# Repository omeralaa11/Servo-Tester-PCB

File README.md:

# Servo Tester PCB

A simple and compact servo tester based on the NE556 timer IC. This project includes a custom-designed PCB layout suitable for testing standard hobby servos.

## 🧰 Features

- Manual PWM signal generation using NE556 timer
- Adjustable pulse width via potentiometer
- Compatible with most RC servos
- Compact and easy-to-fabricate PCB design
- Powered via standard 5V input

## 📝 Project Files

This repository contains:

- `Servo_Tester.kicad_pcb` – PCB layout file (KiCad)
- `Servo_Tester.sch` – Schematic file (KiCad)
- `images/` – Rendered images of the PCB and schematic

## ⚙️ How It Works

The NE556 timer is configured in astable mode to generate a PWM signal. By adjusting the potentiometer, the pulse width of the PWM signal changes, thereby controlling the servo angle.

Typical PWM specs:
- Frequency: ~2.5KHz or 25KHz

## 🔧 Hardware Requirements

- NE556 timer IC
- 2*50k potentiometer
- Resistors and capacitors (see schematic)
- Standard 3-pin servo header
- 5V to 15V power source

## 📸 Gallery

## 🛠️ Usage

1. Connect a 5V power source to the input.
2. Plug in your servo to the output header (GND, VCC, Signal).
3. Rotate the potentiometer to test the servo movement.

## 🧑‍💻 Author

**Omer Alaa**  
🔗 [@omeralaa11](https://github.com/omeralaa11)

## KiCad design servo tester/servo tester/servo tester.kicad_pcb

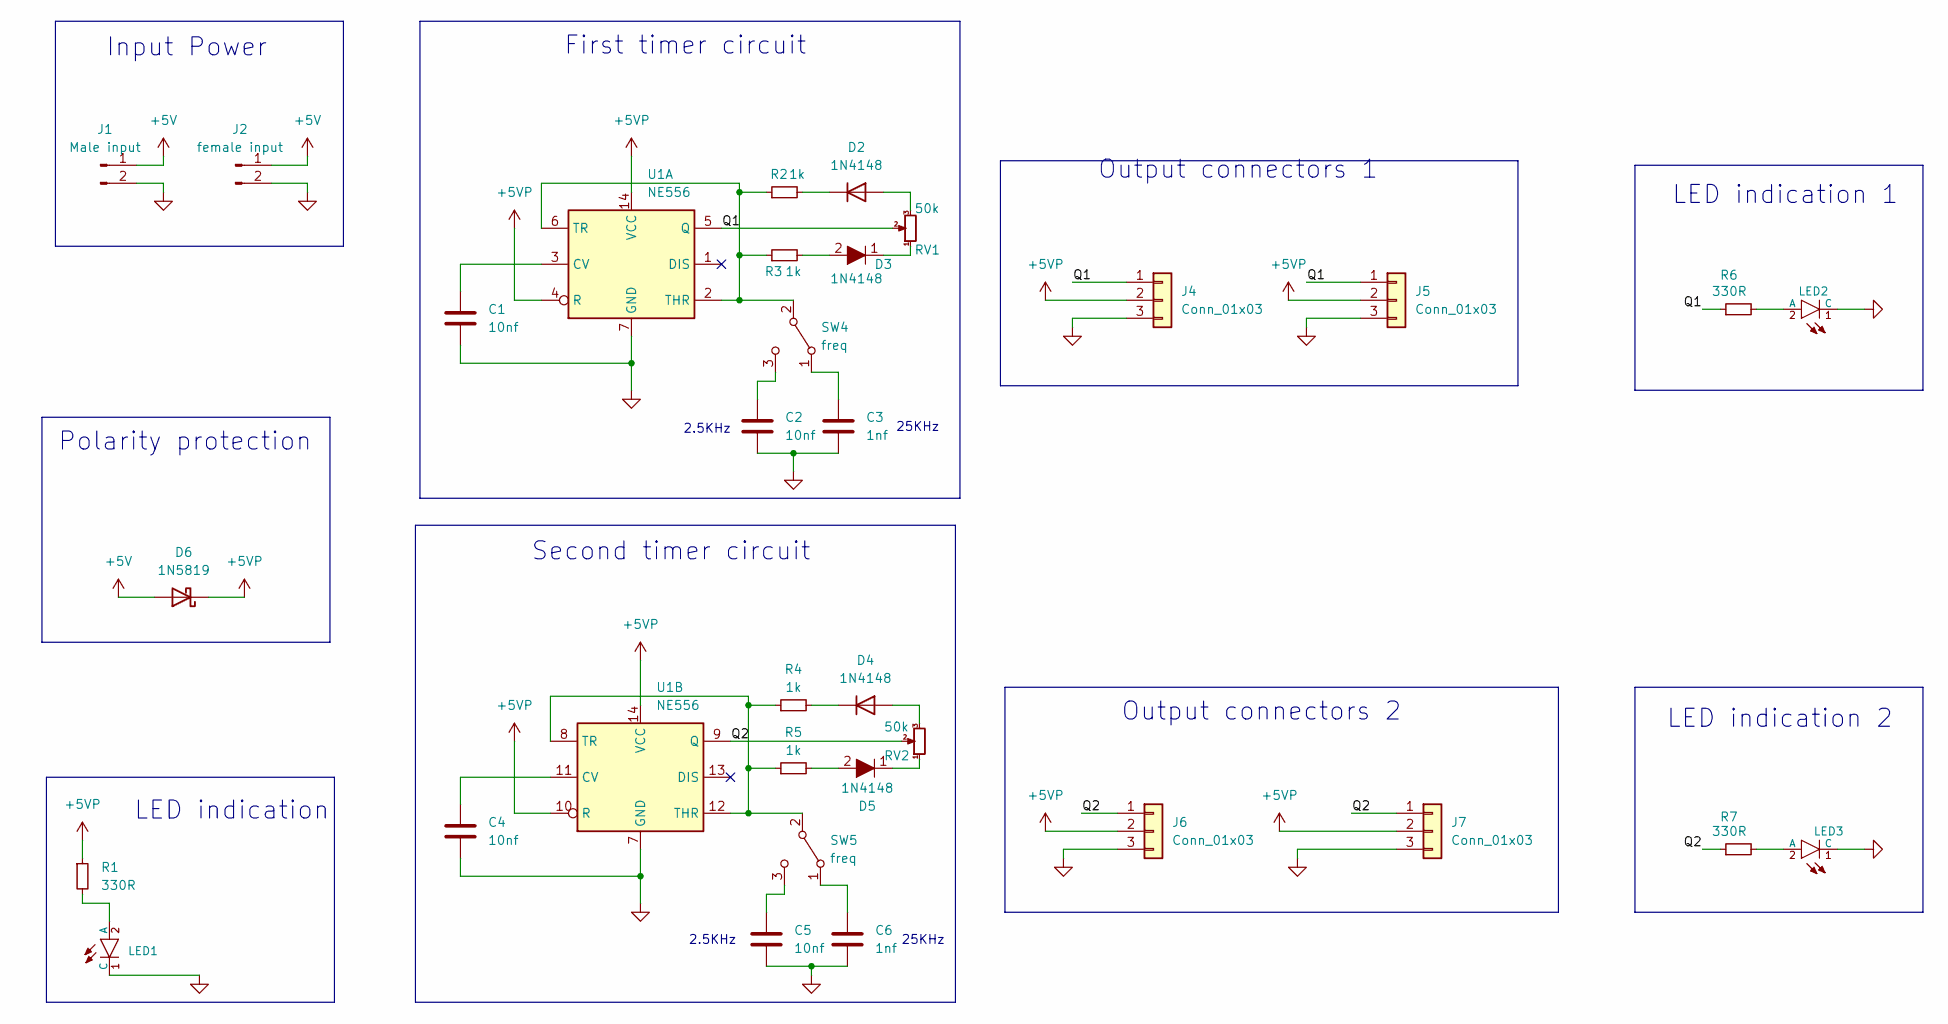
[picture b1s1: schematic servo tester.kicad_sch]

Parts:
C1, C2, C4, C5: 10nf; C_Disc_D6.0mm_W4.4mm_P5.00mm
C3, C6: 1nf; C_Disc_D6.0mm_W4.4mm_P5.00mm
D2, D4: 1N4148; D_DO-35_SOD27_P7.62mm_Horizontal
D3, D5: 1N4148; D_DO-35_SOD27_P7.62mm_Horizontal; MPN 1N4148; Digi-Key_PN 1N4148FS-ND
D6: 1N5819; D_DO-41_SOD81_P10.16mm_Horizontal
J1: Male input; PinHeader_1x02_P2.54mm_Vertical
J2: female input; PinSocket_1x02_P2.54mm_Vertical
J4, J5, J6, J7: Conn_01x03; Pins_1x03_2.54mm_TH; Part Number 1-0301FBV0T
LED1, LED2, LED3: Red_3mm_TH; LED_D3.0mm; Part Number 330HR3C
R1, R6, R7: 330R; R_Axial_DIN0204_L3.6mm_D1.6mm_P7.62mm_Horizontal
R2, R3, R4, R5: 1k; R_Axial_DIN0204_L3.6mm_D1.6mm_P7.62mm_Horizontal
RV1, RV2: 50k; Potentiometer_Alpha_RD901F-40-00D_Single_Vertical
SW4, SW5: freq; Slide_SPDT_PTH_11.6x4.0mm
U1: NE556; DIP-14_W7.62mm

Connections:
+5V: D6.2 (A), J1.1, J2.1; also elsewhere on the board
+5VP: D6.1 (K), J4.2, J5.2, J6.2, J7.2, R1.1, U1.4 (R), U1.10 (R), U1.14 (VCC)
/Q1: J4.1, J5.1, R6.1, RV1.2, U1.5 (Q)
/Q2: J6.1, J7.1, R7.1, RV2.2, U1.9 (Q)
GND: C1.2, C2.2, C3.2, C4.2, C5.2, C6.2, J1.2, J2.2, J4.3, J5.3, J6.3, J7.3, LED1.1 (C), LED2.1 (C), LED3.1 (C), U1.7 (GND); also elsewhere on the board
unnamed: D2.2 (A), RV1.3
unnamed: D2.1 (K), R2.2
unnamed: D3.1, RV1.1
unnamed: D3.2, R3.2
unnamed: D4.2 (A), RV2.3
unnamed: D4.1 (K), R4.2
unnamed: D5.1, RV2.1
unnamed: D5.2, R5.2
unnamed: LED1.2 (A), R1.2
unnamed: LED2.2 (A), R6.2
unnamed: LED3.2 (A), R7.2
unnamed: C3.1, SW4.1 (A)
unnamed: R2.1, R3.1, SW4.2 (B), U1.2 (THR), U1.6 (TR)
unnamed: C2.1, SW4.3 (C)
unnamed: C6.1, SW5.1 (A)
unnamed: R4.1, R5.1, SW5.2 (B), U1.8 (TR), U1.12 (THR)
unnamed: C5.1, SW5.3 (C)
unnamed: C1.1, U1.3 (CV)
unnamed: C4.1, U1.11 (CV)

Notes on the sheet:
Input Power
Second timer circuit
Output connectors 1
LED indication
LED indication 1
2.5KHz
Polarity protection
LED indication 2
25KHz
Output connectors 2
First timer circuit

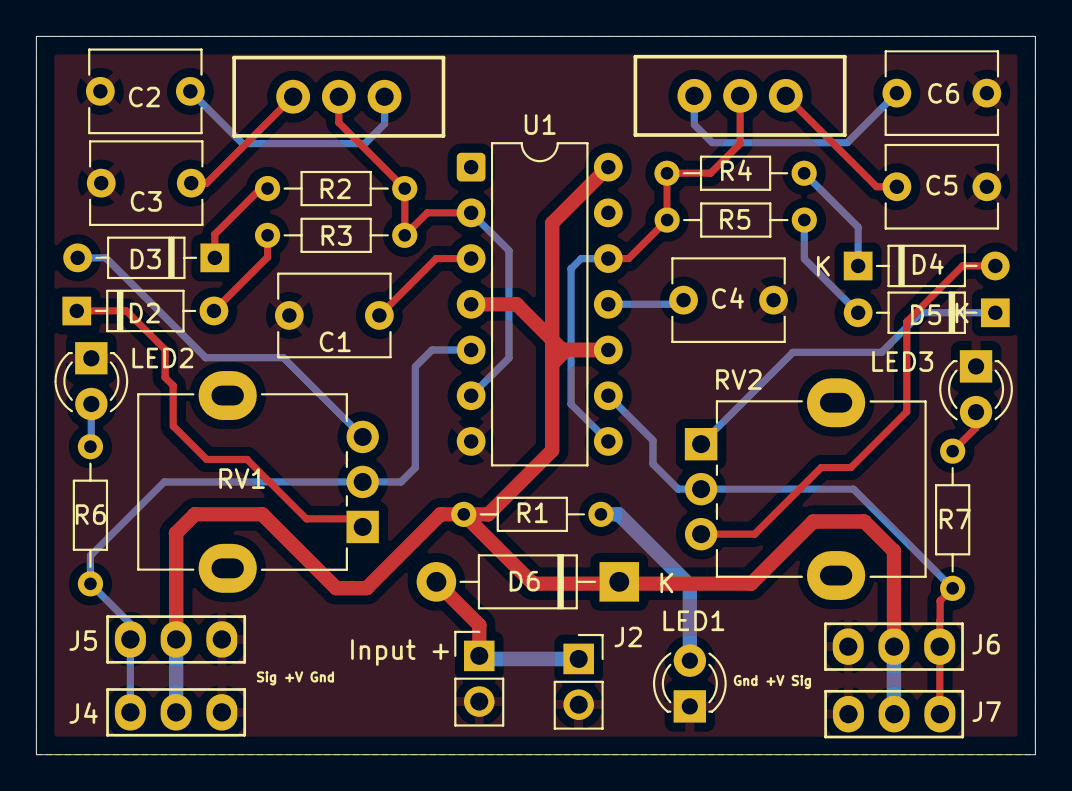
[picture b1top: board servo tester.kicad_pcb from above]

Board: 2 copper layers, 55.5 x 39.9 mm, 32 parts (0 on the bottom side), 24 nets.

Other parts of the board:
Input +: Male input; PinHeader_1x02_P2.54mm_Vertical

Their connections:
+5V: Input +.1; also elsewhere on the board
GND: Input +.2; also elsewhere on the board

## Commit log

2025-06-08 uploaded project files
